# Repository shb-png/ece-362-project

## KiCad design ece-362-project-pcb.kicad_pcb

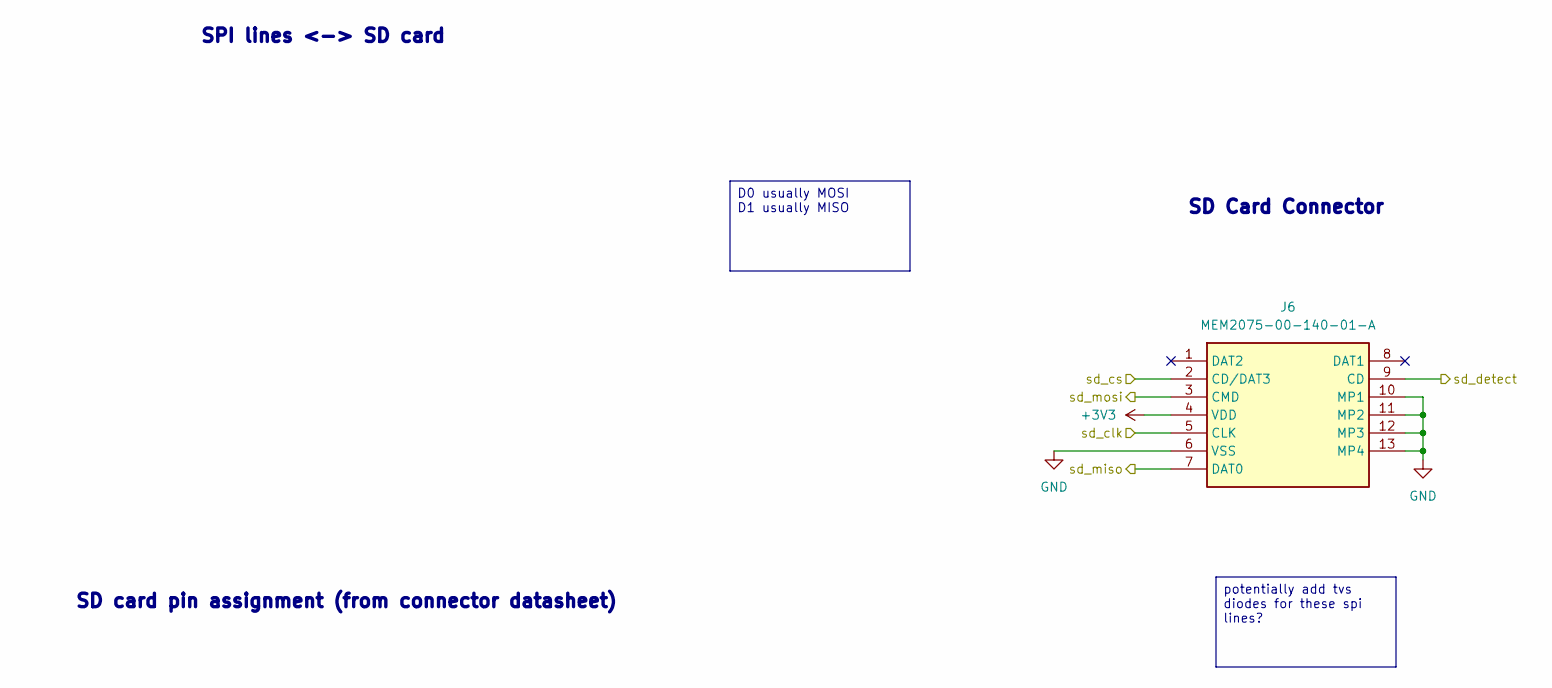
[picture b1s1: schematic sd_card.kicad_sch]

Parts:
J6: MEM2075-00-140-01-A; MEM20750014001A; Manufacturer_Part_Number MEM2075-00-140-01-A; Mouser Part Number 640-MEM20750014001A

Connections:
+3V3: J6.4 (VDD); also elsewhere on the board
/rp2350/sd_clk: J6.5 (CLK); also elsewhere on the board
/rp2350/sd_cs: J6.2 (CD/DAT3); also elsewhere on the board
/rp2350/sd_detect: J6.9 (CD); also elsewhere on the board
/rp2350/sd_miso: J6.7 (DAT0); also elsewhere on the board
/rp2350/sd_mosi: J6.3 (CMD); also elsewhere on the board
GND: J6.6 (VSS), J6.10 (MP1), J6.11 (MP2), J6.12 (MP3), J6.13 (MP4); also elsewhere on the board

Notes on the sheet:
SPI lines <-> SD card
SD card pin assignment (from connector datasheet)
SD Card Connector
potentially add tvs diodes for these spi lines?
D0 usually MOSI D1 usually MISO

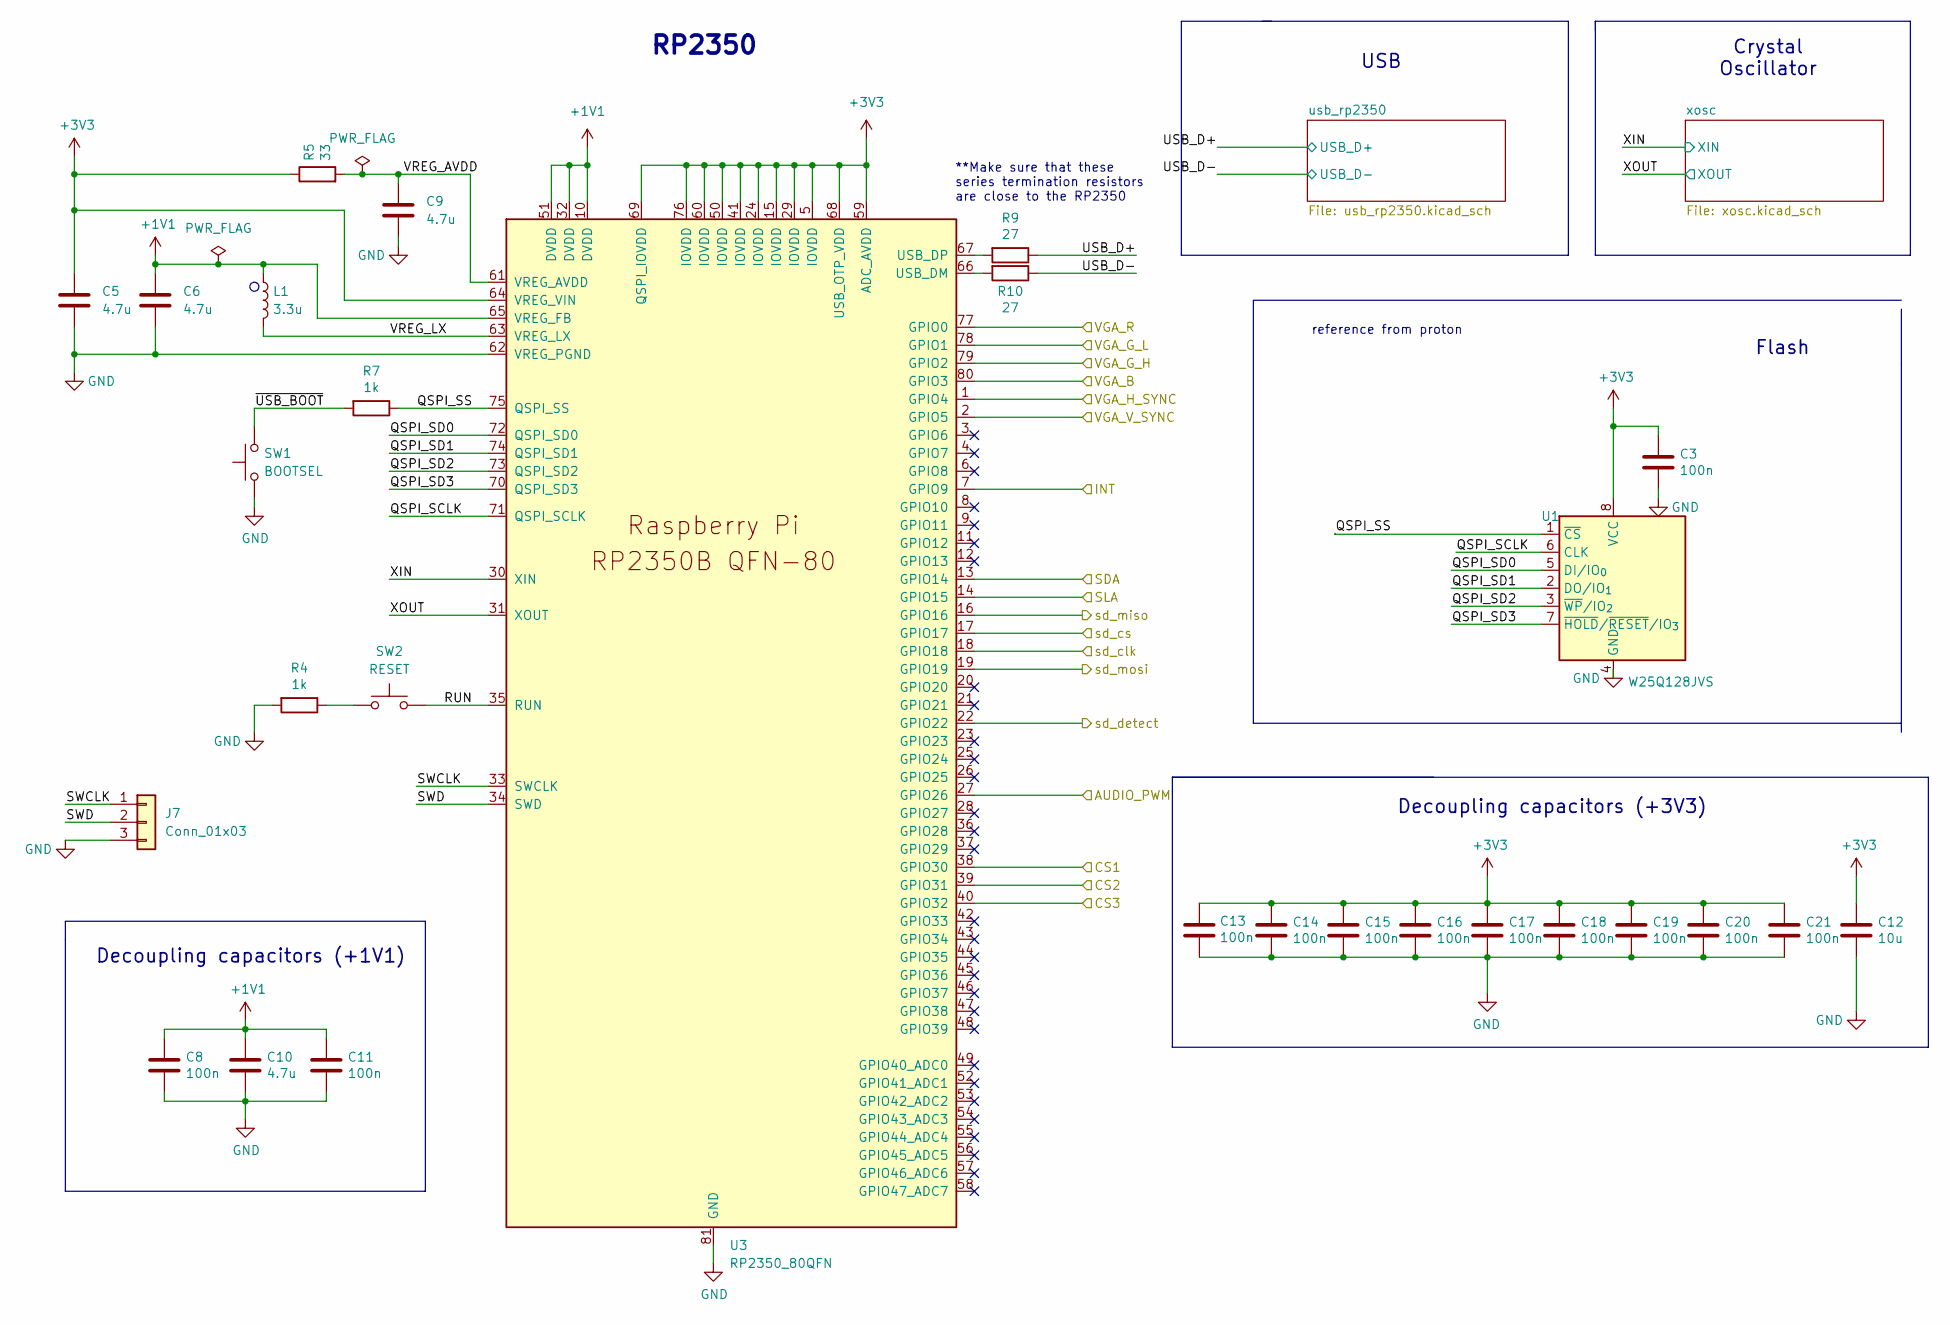
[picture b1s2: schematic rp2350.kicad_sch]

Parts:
C3, C8, C11, C13, C14, C15, C16, C17, C18, C19, C20, C21: 100n; C_0805_2012Metric; MPN CL05B104KP5VPNC
C5, C6, C9, C10: 4.7u; C_0805_2012Metric; MPN CL05A475MP5NRNC
C12: 10u; C_0805_2012Metric; MPN CL21A106KOQNNNE
J7: Conn_01x03; PinHeader_1x03_P2.54mm_Vertical
L1: 3.3u; L_0805_2012Metric_Pad1.05x1.20mm_HandSolder; MPN AOTA-B201610S3R3-101-T
R4, R7: 1k; R_0805_2012Metric_Pad1.20x1.40mm_HandSolder; MPN RC0402JR-071KL
R5: 33; R_0805_2012Metric_Pad1.20x1.40mm_HandSolder; MPN RC0402JR-0733RL
R9, R10: 27; R_0805_2012Metric_Pad1.20x1.40mm_HandSolder; MPN RC0402JR-0727RL
SW1: BOOTSEL; SW_SPST_PTS647_Sx38; MPN PTS647SM38SMTR2 LFS
SW2: RESET; SW_SPST_PTS647_Sx38; MPN PTS647SM38SMTR2 LFS
U1: W25Q128JVS; SOIC-8_5.3x5.3mm_P1.27mm
U3: RP2350_80QFN; QFN-80-1EP_10x10mm_P0.4mm_EP3.4x3.4mm; MPN SC1510-A4

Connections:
+1V1: C6.1, C8.1, C10.1, C11.1, L1.1, U3.10 (DVDD), U3.32 (DVDD), U3.51 (DVDD), U3.65 (VREG_FB)
+3V3: C3.1, C5.1, C12.1, C13.1, C14.1, C15.1, C16.1, C17.1, C18.1, C19.1, C20.1, C21.1, R5.1, U1.8 (VCC), U3.5 (IOVDD), U3.15 (IOVDD), U3.24 (IOVDD), U3.29 (IOVDD), U3.41 (IOVDD), U3.50 (IOVDD), U3.59 (ADC_AVDD), U3.60 (IOVDD), U3.64 (VREG_VIN), U3.68 (USB_OTP_VDD), U3.69 (QSPI_IOVDD), U3.76 (IOVDD); also elsewhere on the board
/audio/AUDIO_PWM: U3.27 (GPIO26); also elsewhere on the board
/capacitve_sensor/CS1: U3.38 (GPIO30); also elsewhere on the board
/capacitve_sensor/CS2: U3.39 (GPIO31); also elsewhere on the board
/capacitve_sensor/CS3: U3.40 (GPIO32); also elsewhere on the board
/capacitve_sensor/INT: U3.7 (GPIO9); also elsewhere on the board
/capacitve_sensor/SCL: U3.14 (GPIO15); also elsewhere on the board
/capacitve_sensor/SDA: U3.13 (GPIO14); also elsewhere on the board
/rp2350/QSPI_SCLK: U1.6 (CLK), U3.71 (QSPI_SCLK)
/rp2350/QSPI_SD0: U1.5 (DI/IO_{0}), U3.72 (QSPI_SD0)
/rp2350/QSPI_SD1: U1.2 (DO/IO_{1}), U3.74 (QSPI_SD1)
/rp2350/QSPI_SD2: U1.3 (~WP/IO_{2}), U3.73 (QSPI_SD2)
/rp2350/QSPI_SD3: U1.7 (~HOLD/~RESET/IO_{3}), U3.70 (QSPI_SD3)
/rp2350/QSPI_SS: R7.1, U1.1 (~CS), U3.75 (QSPI_SS)
/rp2350/RUN: SW2.2, U3.35 (RUN)
/rp2350/SWCLK: J7.1, U3.33 (SWCLK)
/rp2350/SWD: J7.2, U3.34 (SWD)
/rp2350/USB_D+: R9.1; also elsewhere on the board
/rp2350/USB_D-: R10.1; also elsewhere on the board
/rp2350/VGA_B: U3.80 (GPIO3); also elsewhere on the board
/rp2350/VGA_G_H: U3.79 (GPIO2); also elsewhere on the board
/rp2350/VGA_G_L: U3.78 (GPIO1); also elsewhere on the board
/rp2350/VGA_H_SYNC: U3.1 (GPIO4); also elsewhere on the board
/rp2350/VGA_R: U3.77 (GPIO0); also elsewhere on the board
/rp2350/VGA_V_SYNC: U3.2 (GPIO5); also elsewhere on the board
/rp2350/VREG_AVDD: C9.1, R5.2, U3.61 (VREG_AVDD)
/rp2350/VREG_LX: L1.2, U3.63 (VREG_LX)
/rp2350/XIN: U3.30 (XIN); also elsewhere on the board
/rp2350/XOUT: U3.31 (XOUT); also elsewhere on the board
/rp2350/sd_clk: U3.18 (GPIO18); also elsewhere on the board
/rp2350/sd_cs: U3.17 (GPIO17); also elsewhere on the board
/rp2350/sd_detect: U3.22 (GPIO22); also elsewhere on the board
/rp2350/sd_miso: U3.16 (GPIO16); also elsewhere on the board
/rp2350/sd_mosi: U3.19 (GPIO19); also elsewhere on the board
/rp2350/~USB_BOOT: R7.2, SW1.2
GND: C3.2, C5.2, C6.2, C8.2, C9.2, C10.2, C11.2, C12.2, C13.2, C14.2, C15.2, C16.2, C17.2, C18.2, C19.2, C20.2, C21.2, J7.3, R4.2, SW1.1, U1.4 (GND), U3.62 (VREG_PGND), U3.81 (GND); also elsewhere on the board
unnamed: R4.1, SW2.1
unnamed: R10.2, U3.66 (USB_DM)
unnamed: R9.2, U3.67 (USB_DP)

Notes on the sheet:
Crystal Oscillator
USB
reference from proton
Flash
RP2350
**Make sure that these series termination resistors are close to the RP2350
Decoupling capacitors (+3V3)
Decoupling capacitors (+1V1)

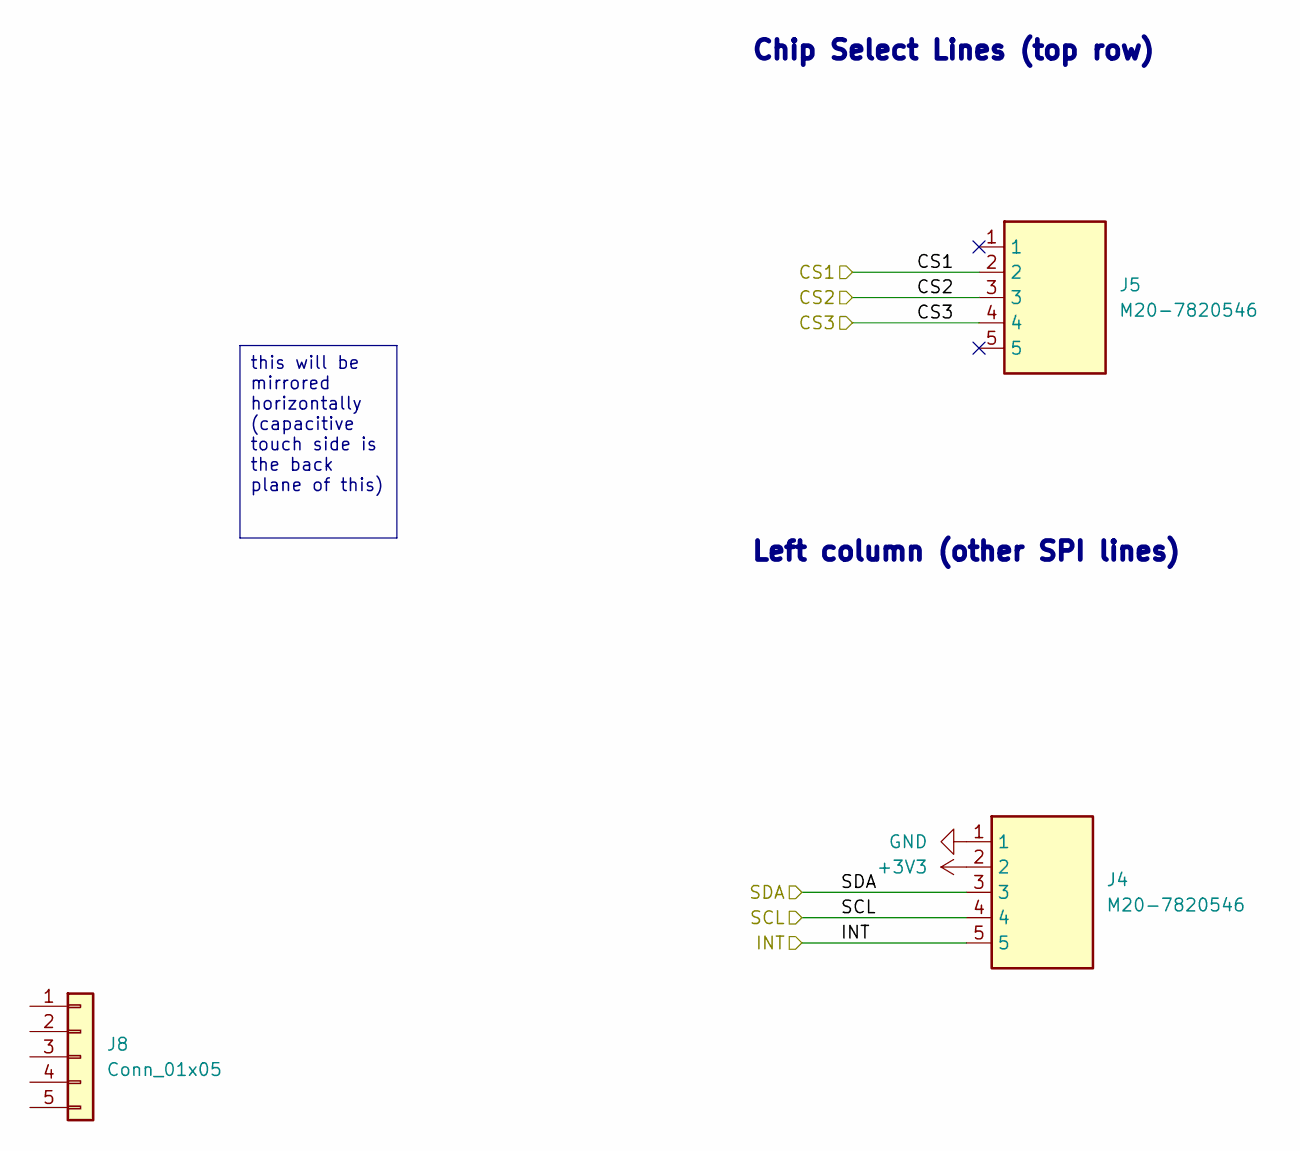
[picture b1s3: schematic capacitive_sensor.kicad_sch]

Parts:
J4, J5: M20-7820546; PinHeader_1x05_P2.54mm_Vertical; Manufacturer_Part_Number M20-7820546; Mouser Part Number 855-M20-7820546
J8: Conn_01x05; PinHeader_1x05_P2.54mm_Vertical

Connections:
+3V3: J4.2; also elsewhere on the board
/capacitve_sensor/CS1: J5.2; also elsewhere on the board
/capacitve_sensor/CS2: J5.3; also elsewhere on the board
/capacitve_sensor/CS3: J5.4; also elsewhere on the board
/capacitve_sensor/INT: J4.5; also elsewhere on the board
/capacitve_sensor/SCL: J4.4; also elsewhere on the board
/capacitve_sensor/SDA: J4.3; also elsewhere on the board
GND: J4.1; also elsewhere on the board

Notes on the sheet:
Left column (other SPI lines)
Chip Select Lines (top row)
this will be mirrored horizontally (capacitive touch side is the back plane of this)

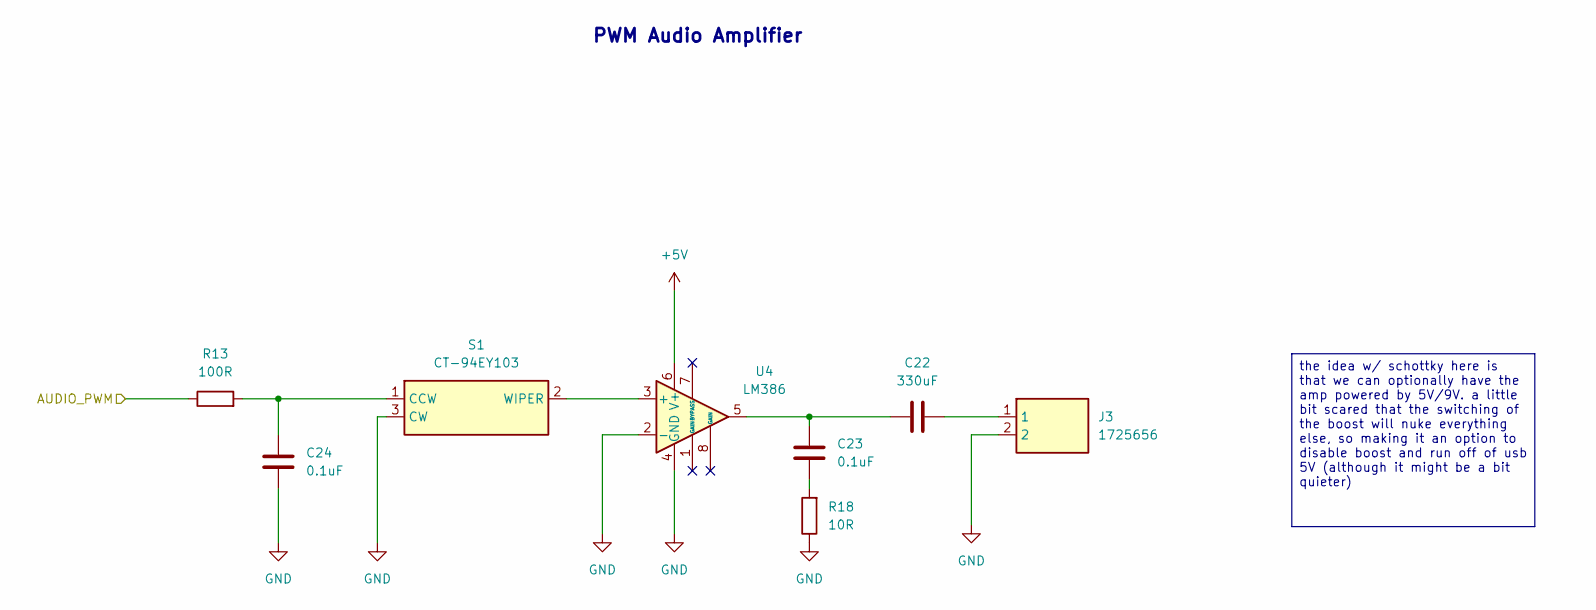
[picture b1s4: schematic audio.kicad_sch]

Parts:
C22: 330uF; C_0805_2012Metric
C23, C24: 0.1uF; C_0805_2012Metric
J3: 1725656; Manufacturer_Part_Number 1725656; Mouser Part Number 651-1725656
R13: 100R; R_0805_2012Metric_Pad1.20x1.40mm_HandSolder
R18: 10R; R_0805_2012Metric_Pad1.20x1.40mm_HandSolder
S1: CT-94EY103; CT94EY103; Manufacturer_Part_Number CT-94EY103; Mouser Part Number 229-CT-94EY103
U4: LM386; DIP-8_W7.62mm

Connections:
+5V: U4.6 (V+); also elsewhere on the board
/audio/AUDIO_PWM: R13.1; also elsewhere on the board
GND: C24.2, J3.2, R18.1, S1.3 (CW), U4.2 (-), U4.4 (GND); also elsewhere on the board
unnamed: C22.1, J3.1
unnamed: C22.2, C23.1, U4.5
unnamed: C23.2, R18.2
unnamed: C24.1, R13.2, S1.1 (CCW)
unnamed: S1.2 (WIPER), U4.3 (+)

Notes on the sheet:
PWM Audio Amplifier
the idea w/ schottky here is that we can optionally have the amp powered by 5V/9V. a little bit scared that the switching of the boost will nuke everything else, so making it an option to disable boost and run off of usb 5V (although it might be a bit quieter)

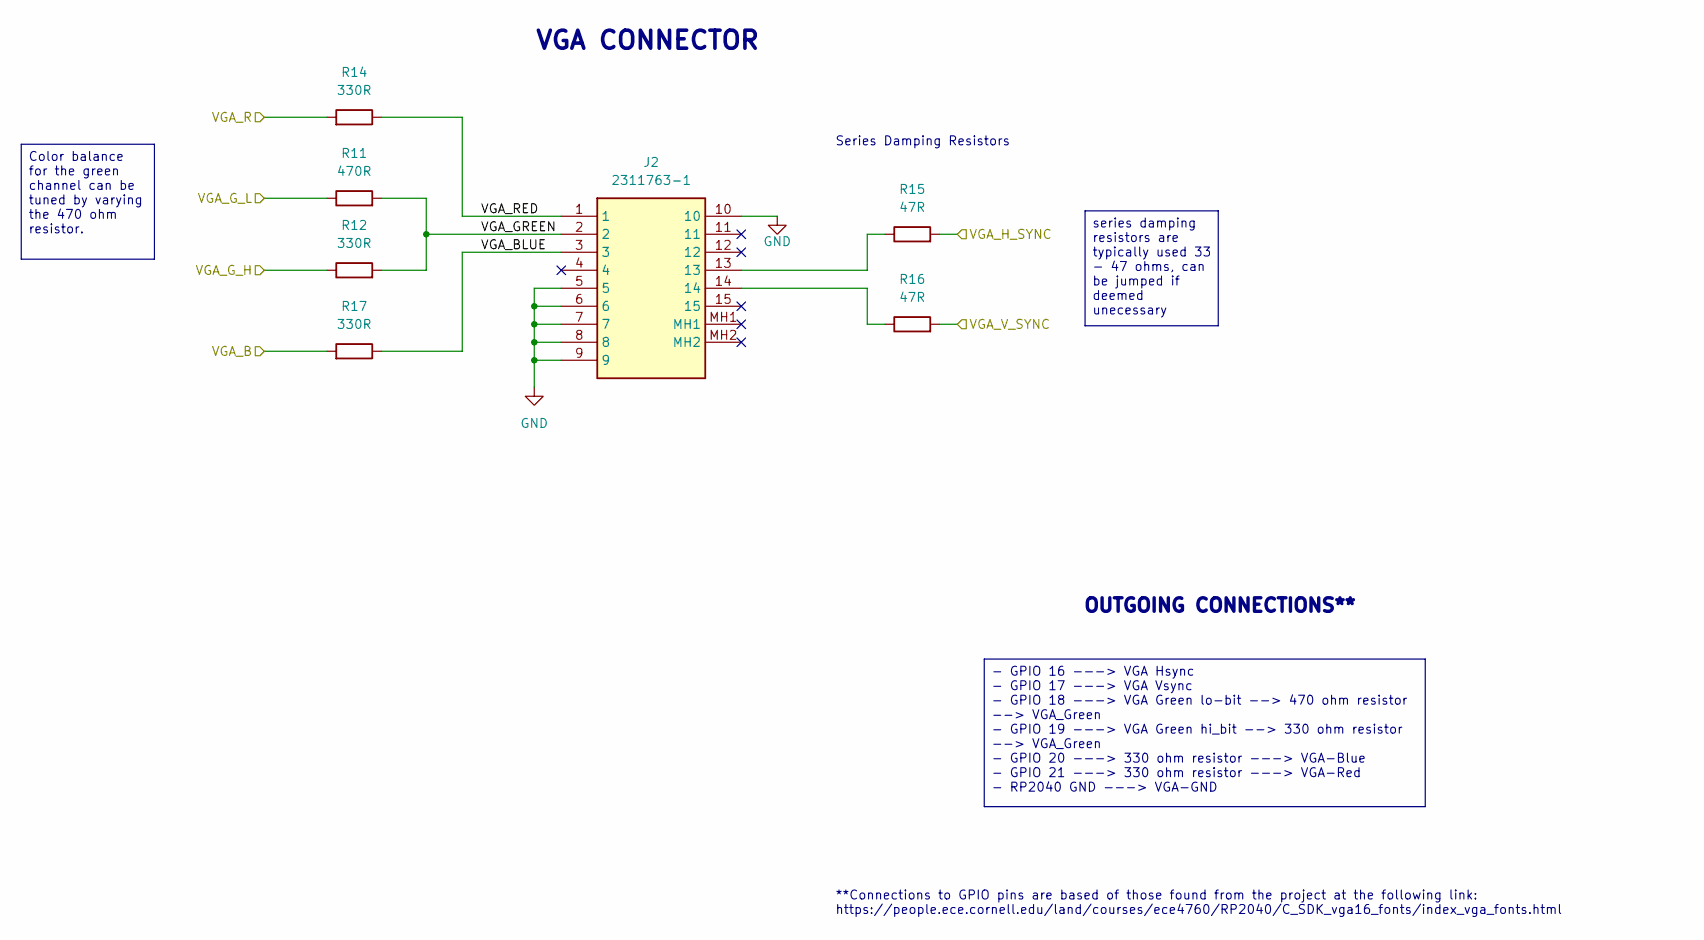
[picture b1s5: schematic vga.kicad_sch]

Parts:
J2: 2311763-1; 23117631; Manufacturer_Part_Number 2311763-1; Mouser Part Number 571-2311763-1
R11: 470R; R_0805_2012Metric_Pad1.20x1.40mm_HandSolder
R12, R14, R17: 330R; R_0805_2012Metric_Pad1.20x1.40mm_HandSolder
R15, R16: 47R; R_0805_2012Metric_Pad1.20x1.40mm_HandSolder

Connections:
/rp2350/VGA_B: R17.2; also elsewhere on the board
/rp2350/VGA_G_H: R12.1; also elsewhere on the board
/rp2350/VGA_G_L: R11.1; also elsewhere on the board
/rp2350/VGA_H_SYNC: R15.2; also elsewhere on the board
/rp2350/VGA_R: R14.2; also elsewhere on the board
/rp2350/VGA_V_SYNC: R16.2; also elsewhere on the board
/vga/VGA_BLUE: J2.3, R17.1
/vga/VGA_GREEN: J2.2, R11.2, R12.2
/vga/VGA_RED: J2.1, R14.1
GND: J2.5, J2.6, J2.7, J2.8, J2.9, J2.10; also elsewhere on the board
unnamed: J2.13, R15.1
unnamed: J2.14, R16.1

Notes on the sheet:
OUTGOING CONNECTIONS**
**Connections to GPIO pins are based of those found from the project at the following link: https://people.ece.cornell.edu/land/courses/ece4760/RP2040/C_SDK_vga16_fonts/index_vga_fonts.html
VGA CONNECTOR
Series Damping Resistors
series damping resistors are typically used 33 - 47 ohms, can be jumped if deemed unecessary
Color balance for the green channel can be tuned by varying the 470 ohm resistor.
- GPIO 16 ---> VGA Hsync - GPIO 17 ---> VGA Vsync - GPIO 18 ---> VGA Green lo-bit --> 470 ohm resistor --> VGA_Green - GPIO 19 ---> VGA Green hi_bit --> 330 ohm resistor --> VGA_Green - GPIO 20 ---> 330 ohm resistor ---> VGA-Blue - GPIO 21 ---> 330 ohm resistor ---> VGA-Red - RP2040 GND ---> VGA-GND

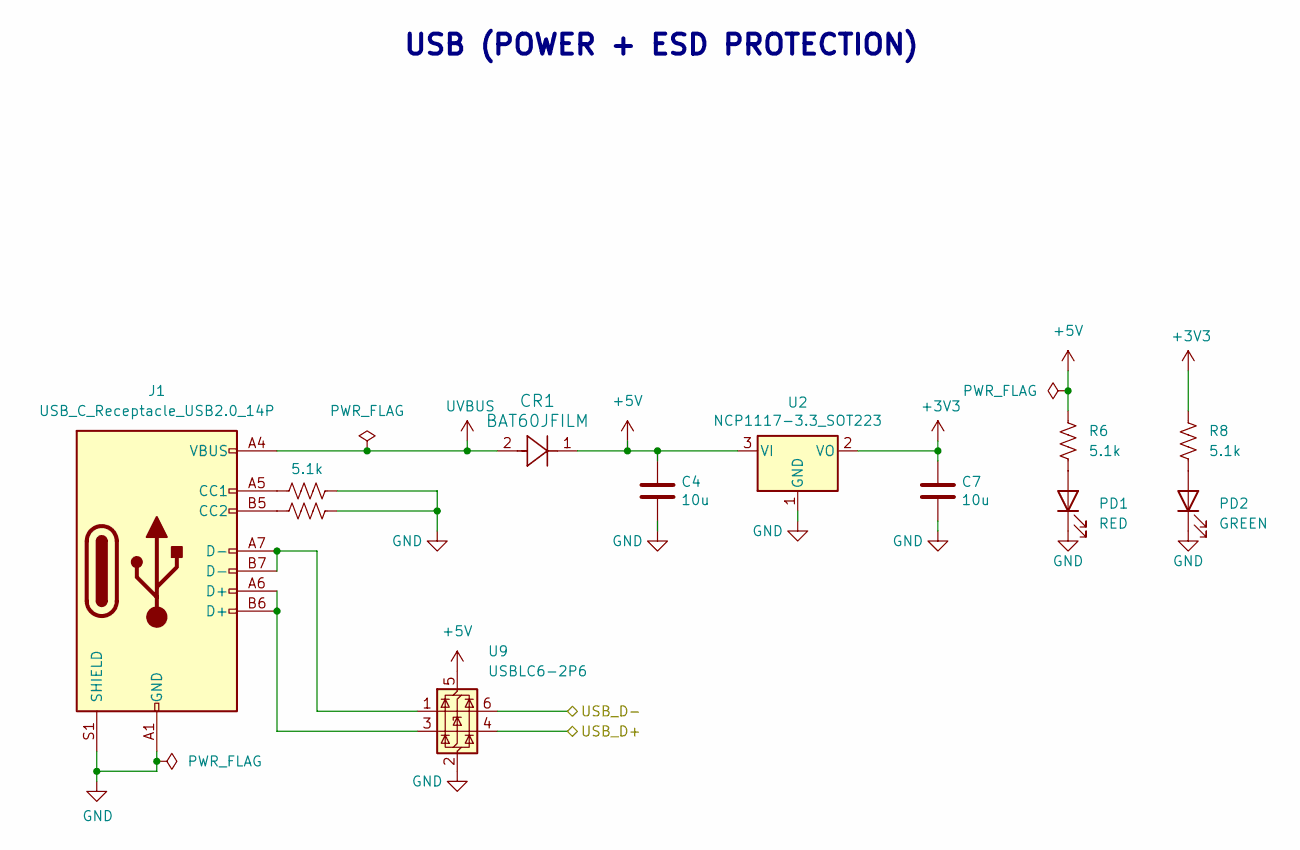
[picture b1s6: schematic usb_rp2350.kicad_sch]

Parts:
C4, C7: 10u; C_0805_2012Metric; MPN CL21A106KOQNNNE
CR1: BAT60JFILM; D_SOD-323_HandSoldering; MPN BAT60A-TR
J1: USB_C_Receptacle_USB2.0_14P; USB_C_Receptacle_G-Switch_GT-USB-7010ASV; MPN UJ20-C-H-G-SMT-1-P16-TR
PD1: RED; LED_0805_2012Metric; MPN LS R976-NR-1-0-20-R18
PD2: GREEN; LED_0805_2012Metric; MPN LG R971-KN-1-0-20-R18
R1, R2, R6, R8: 5.1k; R_0805_2012Metric_Pad1.20x1.40mm_HandSolder; MPN RK73H1ETTP5101F
U2: NCP1117-3.3_SOT223; SOT-223-3_TabPin2; MPN NCP1117LPST33T3G
U9: USBLC6-2P6; SOT-666; MPN USBLC6-2P6

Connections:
+3V3: C7.1, R8.1, U2.2 (VO); also elsewhere on the board
+5V: C4.1, CR1.1, R6.1, U2.3 (VI), U9.5 (VBUS); also elsewhere on the board
/rp2350/USB_D+: U9.4 (I/O2); also elsewhere on the board
/rp2350/USB_D-: U9.6 (I/O1); also elsewhere on the board
GND: C4.2, C7.2, J1.A1 (GND), J1.A12 (GND), J1.B1 (GND), J1.B12 (GND), J1.S1 (SHIELD), PD1.1 (K), PD2.1 (K), R1.2, R2.2, U2.1 (GND), U9.2 (GND); also elsewhere on the board
unnamed: J1.A5 (CC1), R1.1
unnamed: J1.B5 (CC2), R2.1
unnamed: J1.A6 (D+), J1.B6 (D+), U9.3 (I/O2)
unnamed: J1.A7 (D-), J1.B7 (D-), U9.1 (I/O1)
unnamed: PD1.2 (A), R6.2
unnamed: PD2.2 (A), R8.2
UVBUS: CR1.2, J1.A4 (VBUS), J1.A9 (VBUS), J1.B4 (VBUS), J1.B9 (VBUS)

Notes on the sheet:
USB (POWER + ESD PROTECTION)

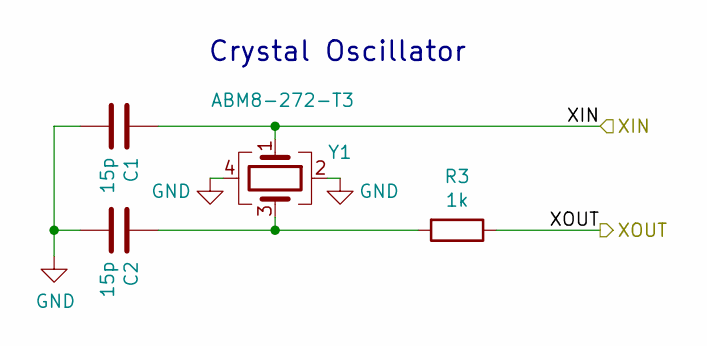
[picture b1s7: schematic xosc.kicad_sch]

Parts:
C1, C2: 15p; C_0805_2012Metric; MPN GJM1555C1H150GB01D
R3: 1k; R_0805_2012Metric_Pad1.20x1.40mm_HandSolder; MPN RC0402JR-071KL
Y1: ABM8-272-T3; Crystal_SMD_3225-4Pin_3.2x2.5mm; MPN ABM8-272-T3

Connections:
/rp2350/XIN: C1.1, Y1.1; also elsewhere on the board
/rp2350/XOUT: R3.1; also elsewhere on the board
GND: C1.2, C2.2, Y1.2, Y1.4; also elsewhere on the board
unnamed: C2.1, R3.2, Y1.3

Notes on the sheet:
Crystal Oscillator

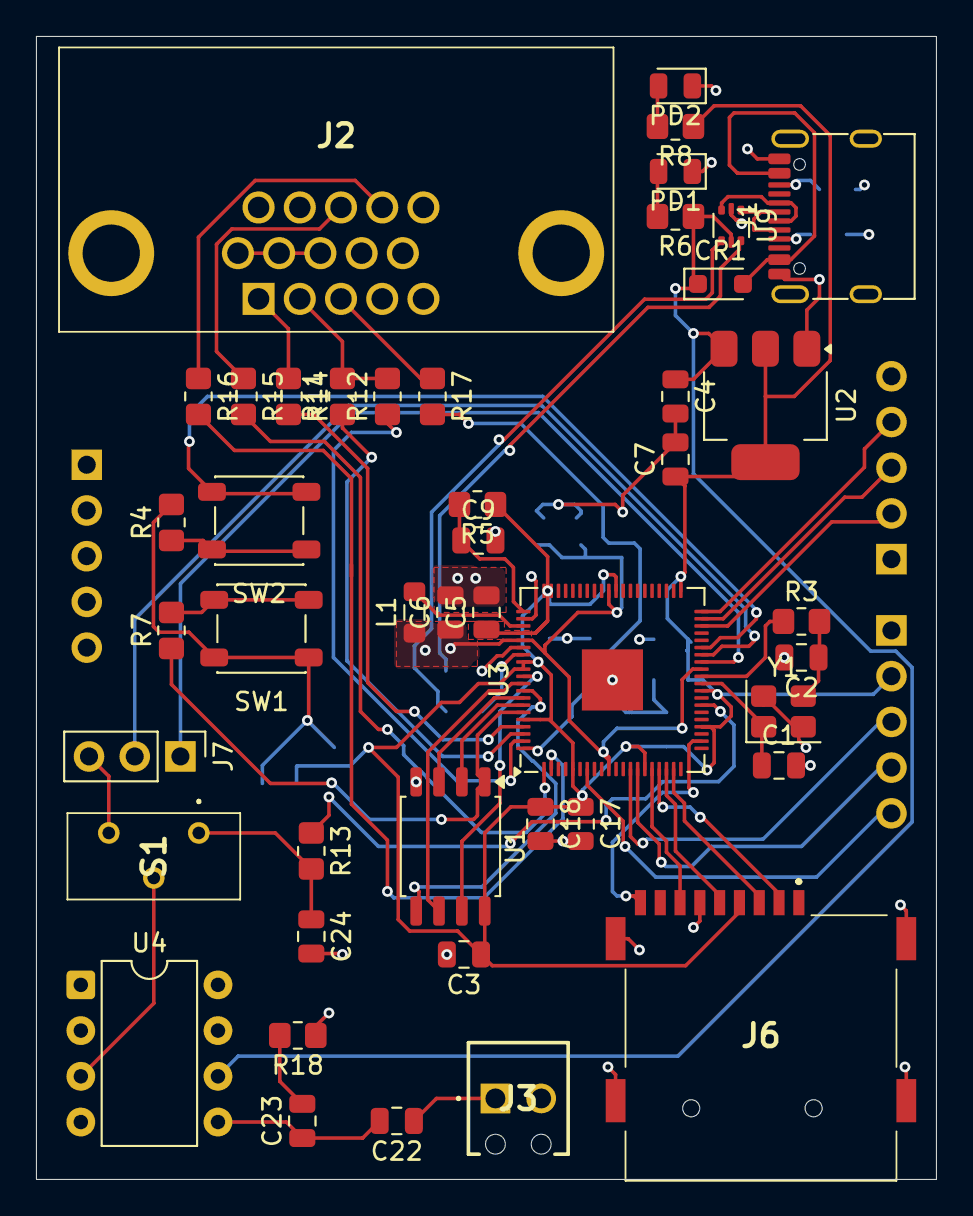
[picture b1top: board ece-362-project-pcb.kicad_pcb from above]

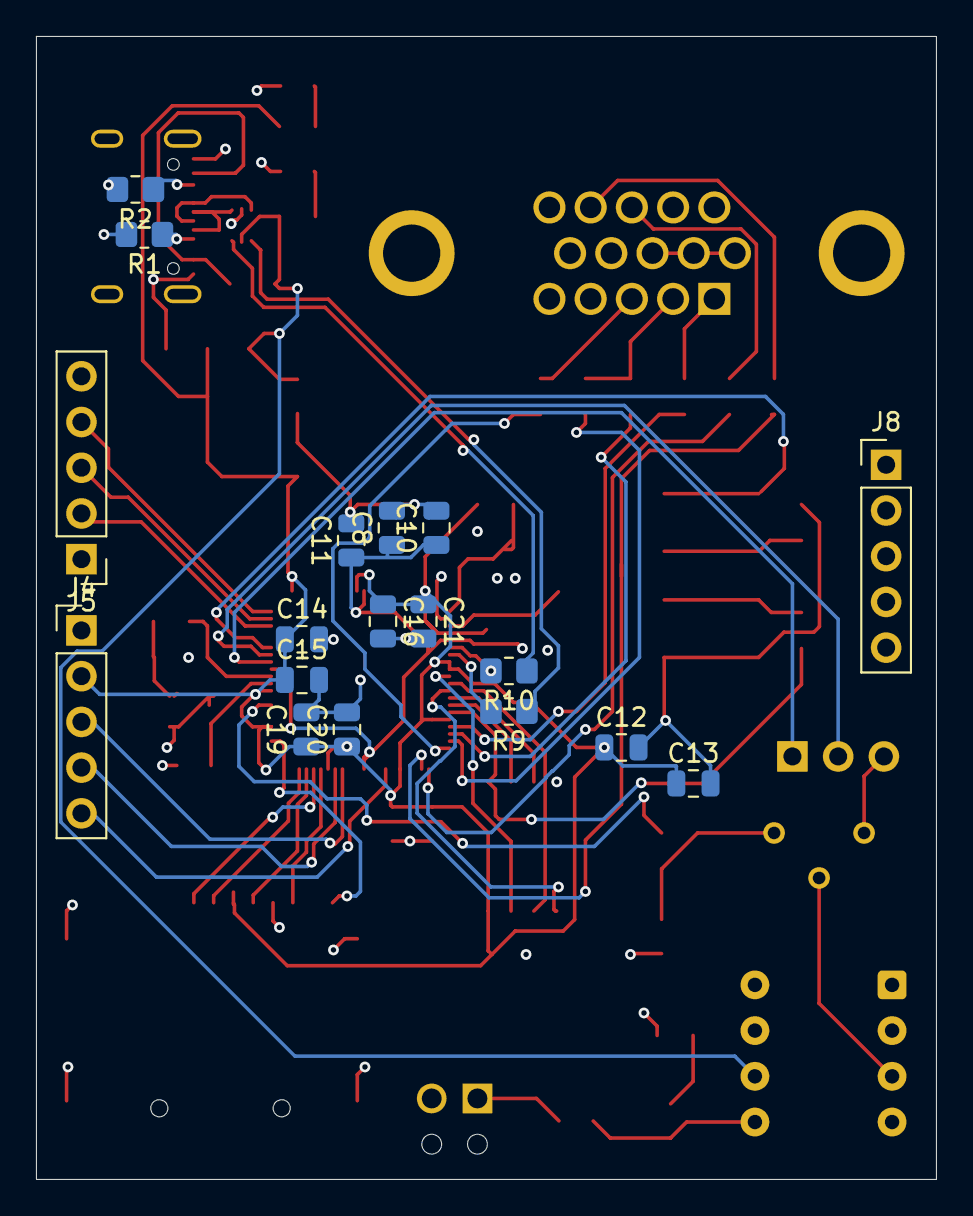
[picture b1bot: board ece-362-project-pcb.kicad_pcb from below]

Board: 4 copper layers, 50.0 x 63.5 mm, 63 parts (18 on the bottom side), 59 nets.
